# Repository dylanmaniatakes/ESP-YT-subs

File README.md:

# ESP YouTube Subscriber Counter

A compact, Wi-Fi-connected YouTube subscriber counter for a Seeed Studio **XIAO ESP32-C6** and a 480×320 SPI display with an ILI9488-compatible controller and XPT2046/ADS7846-compatible touch controller.

The device shows the public subscriber count, total views, public video count, connection status, and an Eastern-time clock. It stores Wi-Fi and YouTube API credentials only in the ESP32's internal preferences; no credentials are committed to this repository.

## What you need

- Seeed Studio XIAO ESP32-C6
- 480×320 SPI display with an ILI9488-compatible controller and XPT2046/ADS7846-compatible touch controller
- USB-C **data** cable — not a charge-only cable
- Jumper wires or the optional KiCad carrier board
- 3.3 V logic; do **not** connect a 5 V-only display directly

The display wiring is documented in [`hardware/xiao_c6_tinylcd_bottom_wiring.svg`](hardware/xiao_c6_tinylcd_bottom_wiring.svg).

## Choose how to install the firmware

There are three ways to put the firmware on the XIAO:

1. **Use the hosted web flasher** — easiest; no command line.
2. **Use the local web flasher** — useful offline or for testing.
3. **Build and upload with Arduino** — useful if you want to modify the firmware.

### Option 1: Hosted web flasher (recommended)

This is the easiest path if you only want to use the project. You do not need Arduino, a terminal, or a custom build.

Web Serial is the browser feature that lets a web page ask permission to use the XIAO’s USB serial connection. Chrome, Brave, and Edge support it.

Open this page on the computer connected to the XIAO:

[Open the ESP-YT web flasher](https://dylanmaniatakes.github.io/ESP-YT-subs/web/)

Then:

1. Connect the XIAO to the computer with a USB-C data cable.
2. Click **Start flashing**.
3. When the browser asks for a serial port, select the XIAO.
4. Wait for the progress bar to reach 100%.
5. Unplug and reconnect the XIAO.

A few things are normal:

- The browser may list other serial devices, including Bluetooth devices. Choose only the XIAO.
- If the XIAO does not appear, hold its **BOOT** button while plugging it in, then click **Try again**.
- The flasher checks the bundled firmware’s SHA-256 checksum and refuses to flash a non-ESP32-C6 chip.

Because the hosted page is served over HTTPS, the browser can open the normal Web Serial device chooser.

### Option 2: Local web flasher

Use this if you want an offline copy or do not want to use the hosted page.

1. Start a small local web server from the repository root:

   ```sh
   python3 -m http.server 8000
   ```

2. Open:

   <http://127.0.0.1:8000/web/>

3. Click **Start flashing** and choose the XIAO in the browser prompt.
4. Wait for the progress bar to finish, then unplug and reconnect the device.

Do **not** open `web/index.html` directly from Finder or VS Code. Web Serial needs the `http://127.0.0.1` origin, so the device chooser will not appear from a `file://` page.

### Option 3: Build and upload with Arduino

Use this if you want to change the firmware.

1. Install [Arduino IDE 2](https://www.arduino.cc/en/software) or [Arduino CLI](https://arduino.github.io/arduino-cli/).
2. Install the **esp32** board package.
3. Select the **XIAO_ESP32C6** board.
4. Use the bundled Adafruit GFX and Adafruit BusIO libraries in [`libraries/`](libraries/), or install those two libraries through the Arduino Library Manager.

#### Arduino IDE

1. Open `firmware/esp_yt_subscriber_counter/esp_yt_subscriber_counter.ino`.
2. Select **XIAO_ESP32C6**.
3. Click **Verify**, then **Upload**.

#### Arduino CLI

```sh
arduino-cli compile \
  --fqbn esp32:esp32:XIAO_ESP32C6:PartitionScheme=huge_app \
  --libraries libraries \
  --output-dir build/esp_yt_subscriber_counter \
  firmware/esp_yt_subscriber_counter

arduino-cli upload \
  --port /dev/YOUR_SERIAL_PORT \
  --fqbn esp32:esp32:XIAO_ESP32C6:PartitionScheme=huge_app \
  --input-dir build/esp_yt_subscriber_counter
```

Replace `/dev/YOUR_SERIAL_PORT` with your actual serial port.

## First-run setup

The firmware does not contain your Wi-Fi password, YouTube handle, or API key.

1. Power the counter.
2. Join the `ESP-YT-Setup` Wi-Fi hotspot.
3. Enter the hotspot password: `setup-subs`.
4. Open `http://192.168.4.1/`.
5. Select your Wi-Fi network, enter its password, enter your YouTube channel handle, and paste your YouTube Data API v3 key.
6. Save.

The counter reboots, joins your network, and starts showing your public channel statistics.

To reset the saved setup later, hold the XIAO’s **BOOT** button while powering it on. The device will clear its saved settings and return to the setup hotspot.

## Features

- Public YouTube channel statistics using YouTube Data API v3
- Captive Wi-Fi setup portal on first boot
- Automatic retry after network, DNS, time, or API failures
- Single tap to switch between the subscriber dashboard and clock
- Double tap to rotate the display 180°
- BOOT-button reset for saved settings
- Optional KiCad carrier board for a cleaner build

## API key notes

Create a YouTube Data API v3 key from [Google Cloud Console](https://console.cloud.google.com/), and restrict it to YouTube Data API v3.

Do not put the API key in the source code. The device asks for it during first-run setup and stores it locally.

## Optional KiCad carrier board

The editable KiCad project is in [`hardware/tinylcd_xiao_ups_carrier_r2/`](hardware/tinylcd_xiao_ups_carrier_r2/README.md).

- KiCad schematic ERC and PCB DRC pass with no reported errors.
- The routed PCB and manufacturing files are included.
- **This board has not been fully fabricated or bench-tested yet.** Treat it as an unverified design until you have built and tested your own copy.
- If you use the 18650 backup-power circuit, follow the safety procedure in the hardware README.

## Repository layout

```text
firmware/esp_yt_subscriber_counter/  Counter firmware
firmware/xiao_c6_ili9488_test/       Display diagnostic firmware
hardware/                            Wiring diagram and KiCad carrier project
releases/                           Prebuilt merged firmware for the web flasher
web/                                Local Web Serial flasher
libraries/                           Bundled Adafruit graphics libraries
```

## License

Project code and hardware files are released under the [MIT License](LICENSE). Bundled third-party libraries retain their own licenses in their respective folders.

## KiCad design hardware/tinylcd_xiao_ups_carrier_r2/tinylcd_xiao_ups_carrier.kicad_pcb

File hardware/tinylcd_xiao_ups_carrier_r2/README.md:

# TinyLCD + XIAO ESP32-C6 18650 UPS carrier R2

This is the corrected 100 x 60 mm, two-layer R2 carrier for the subscriber counter. It holds the XIAO ESP32-C6 in removable 2.54 mm sockets, presents the TinyLCD P9 wiring on one straight 1x11 male header, and adds protected single-cell 18650 charging and automatic backup power.

R2 corrects the R1 right-side XIAO socket ordering. With the XIAO component side up and USB-C toward the board's `USB-C` marking, J2 is `VBUS, GND, 3V3, D10, D9, D8, D7` from top to bottom.

The PCB silkscreen includes a neutral project mark. This branding is independent of the firmware's configurable YouTube channel handle.

The backside silkscreen labels every XIAO socket position. J1 is marked `D0` through `D6`; J2 is marked `5V`, `GND`, `3V3`, `D10`, `D9`, `D8`, and `D7`, starting at the USB-C end.

The P9 display header is labeled the same way on the backside, with `3V3`, `RS`, `MOSI`, `CS`, `SCLK`, `RST`, `BL`, `GND`, `T_IRQ`, `T_CS`, and `T_DOUT` printed beside their corresponding pins.

## Status

- KiCad 10 schematic ERC: **0 errors, 0 warnings**
- KiCad 10 PCB DRC: **0 violations, 0 unconnected pads**
- Fully routed two-layer PCB and filled ground planes
- Gerber/drill order ZIP, JLCPCB BOM, and JLCPCB component placement file generated
- Existing display-to-XIAO signal mapping comes from the physically working subscriber counter
- The display plug is assumed to be the photographed 1x11 **2.54 mm Dupont-style** female connector. Check its pitch with a ruler or calipers before ordering; the photos cannot prove the mechanical pitch to manufacturing tolerance.
- **R2 has passed local CAD checks but has not yet been fabricated or electrically bench-tested. Inspect the fabrication preview before ordering.**

## Files

- `tinylcd_xiao_ups_carrier.kicad_pro` — open this project in KiCad
- `tinylcd_xiao_ups_carrier.kicad_sch` — editable schematic
- `tinylcd_xiao_ups_carrier.kicad_pcb` — routed PCB
- `renders/tinylcd_xiao_ups_carrier_schematic.pdf` — printable schematic
- `drc_report.txt` and `erc_report.txt` — final KiCad check reports
- `manufacturing/tinylcd_xiao_ups_carrier_r2_gerbers.zip` — upload this for bare boards
- `manufacturing/jlcpcb_bom.csv` — top-side SMT assembly BOM
- `manufacturing/jlcpcb_cpl.csv` — top-side SMT placement file
- `manufacturing/manual_parts.csv` — parts to solder after JLCPCB assembly
- `manufacturing/single_board_hand_assembly_bom.csv` — one-board shopping BOM with current supplier links
- `manufacturing/lcsc_upload_bom_single_board.csv` — LCSC upload BOM using order quantities that meet the listed minimums
- `manufacturing/digikey_upload_bom_single_board.csv` — DigiKey upload BOM for the exact battery holder
- `SINGLE_BOARD_SHOPPING_LIST.md` — human-readable sourcing and hand-assembly guide

## TinyLCD connector

`J3` is a straight 1x11, 2.54 mm male header. The board silkscreen marks **P9 PIN 1**. Pin 1 is the end nearest the XIAO/USB-C label.

| P9 pin | TinyLCD label | Carrier destination | Default |
|---:|---|---|---|
| 1 | 3V3 | XIAO 3V3 | Connected |
| 2 | RS | XIAO D0 / GPIO0 | Connected |
| 3 | MOSI | XIAO D10 / GPIO18 | Connected |
| 4 | CS | XIAO D9 / GPIO20 | Connected |
| 5 | SCLK | XIAO D8 / GPIO19 | Connected |
| 6 | RST | XIAO D3 / GPIO21 | Connected |
| 7 | BL | SJ1 to 3V3 | Open |
| 8 | GND | GND | Connected |
| 9 | T_IRQ | SJ2 to XIAO D1 | Open |
| 10 | T_CS | SJ3 to XIAO D2 | Open |
| 11 | T_DOUT | SJ4 to XIAO D4 | Open |

Leave `SJ1` open. For touch operation, close `SJ2`, `SJ3`, and `SJ4`, or use temporary jumpers for the equivalent connections: `T_IRQ` to XIAO D1, `T_CS` to D2, and `T_DOUT` to D4. LCD MOSI/D10 and SCLK/D8 are shared with the touch controller.

## Power design

The XIAO USB-C connector remains the normal input. Its 5V rail powers the XIAO/display and a TP4056 single-cell charger. With USB absent, the protected cell feeds the XIAO 5V input through a P-channel load switch and SS34 Schottky diode. When USB returns, its higher voltage automatically takes over without back-feeding the cell.

- TP4056 charge current: approximately 400 mA (`R1 = 3.0k`)
- Charge temperature sensing: 10k B3950 NTC beside the holder
- Cell protection: DW01A + FS8205A (over-charge, over-discharge, and over-current protection)
- Additional input protection: 1.1A resettable fuse and reverse-polarity P-MOSFET
- `S1`: disables battery backup only; USB operation and charging remain available
- `S1` drives `Q3`'s gate, so the display current does not pass through the 300 mA switch contacts
- `D2` red: charging; `D3` green: charge complete

This is seamless backup for short power failures, not a regulated 5V boost supply. On battery, the XIAO 5V pin receives approximately the cell voltage minus the Schottky drop. That follows Seeed's documented external-battery-to-5V-pin diode arrangement, but the finished prototype must still be tested across the full cell discharge range with this particular display.

## JLCPCB order

### Bare boards only

1. Upload `manufacturing/tinylcd_xiao_ups_carrier_r2_gerbers.zip` to JLCPCB.
2. Use: 2 layers, 1.6 mm FR-4, 1 oz copper, green solder mask, and HASL lead-free or ENIG.
3. The detected board size should be 100 x 60 mm. Do not continue if the dimensions or outline differ.

### SMT-assembled boards

1. Start with the same Gerber ZIP and enable top-side PCB assembly.
2. Upload `manufacturing/jlcpcb_bom.csv` and `manufacturing/jlcpcb_cpl.csv`.
   The CPL intentionally uses negative Y coordinates to match KiCad's Gerber
   manufacturing-coordinate convention for this board. Do not convert them to
   positive values before uploading.
3. Confirm every designator maps to the expected LCSC part. Inventory and catalog mappings change, so approve substitutions only after matching value, package, pinout, voltage/current ratings, and polarity.
4. Inspect the graphical placement preview. Pay special attention to `D1`, `D2`, `D3`, `Q1`, `Q2`, `Q3`, `U1`, `U2`, and the switch orientation.
5. `B1`, `J1`, `J2`, and `J3` are intentionally omitted from the SMT BOM; install those manually.

## Hand assembly

1. Do **not** install a cell yet.
2. Solder the two 1x7 female headers into `J1` and `J2`. Use the XIAO with temporary male headers as an alignment jig, but do not heat the XIAO excessively.
3. Solder a straight 1x11 male header into `J3`.
4. Solder the Keystone 1042 holder into `B1`, matching its positive contact to the large board `+` mark.
5. Solder male headers to the XIAO and insert it with USB-C toward the board's `USB-C` marking.
6. Keep `SJ1` open. Initially leave the touch links open for the power test; after the display works, close `SJ2`, `SJ3`, and `SJ4` to enable touch.

## First-power test

Li-ion mistakes can cause fire. Use eye protection, a nonflammable work surface, and a current-limited USB source for the first test. Never use a damaged cell, never short the holder, and never insert an 18650 backwards.

1. With no XIAO, display, USB, or cell connected, check for shorts between `SYS_5V`, `3V3`, `PACK_POS`, and GND.
2. Set `S1` to battery OFF. Connect current-limited USB and confirm about 5V at the XIAO 5V socket and no abnormal heating.
3. Remove USB. Verify the holder polarity with a meter, then insert one reputable 3.6/3.7V 18650 in the marked direction.
4. Reconnect USB. Confirm the red charge LED behavior and monitor `U1`, the cell, and the holder for heat. Stop immediately if anything becomes hot, smells unusual, or draws unexpected current.
5. Install the XIAO only after the rail checks pass. Test the dashboard on USB before attaching the display cable.
6. Attach the ribbon with P9 pin 1 aligned to `J3` pin 1. Confirm 3.3V and GND orientation before power-up.
7. Turn battery backup ON, run from USB, then unplug USB. The counter should remain running. Test again with a partly discharged cell before considering the design validated.

## Regeneration note

`tools/generate_board.py` produces the unrouted placement/netlist board; the committed `.kicad_pcb` also includes the final routed copper. Do not run that script over the finished PCB unless you intend to route it again. `tools/generate_schematic.py` requires the third-party `kicad-sch-api` package.

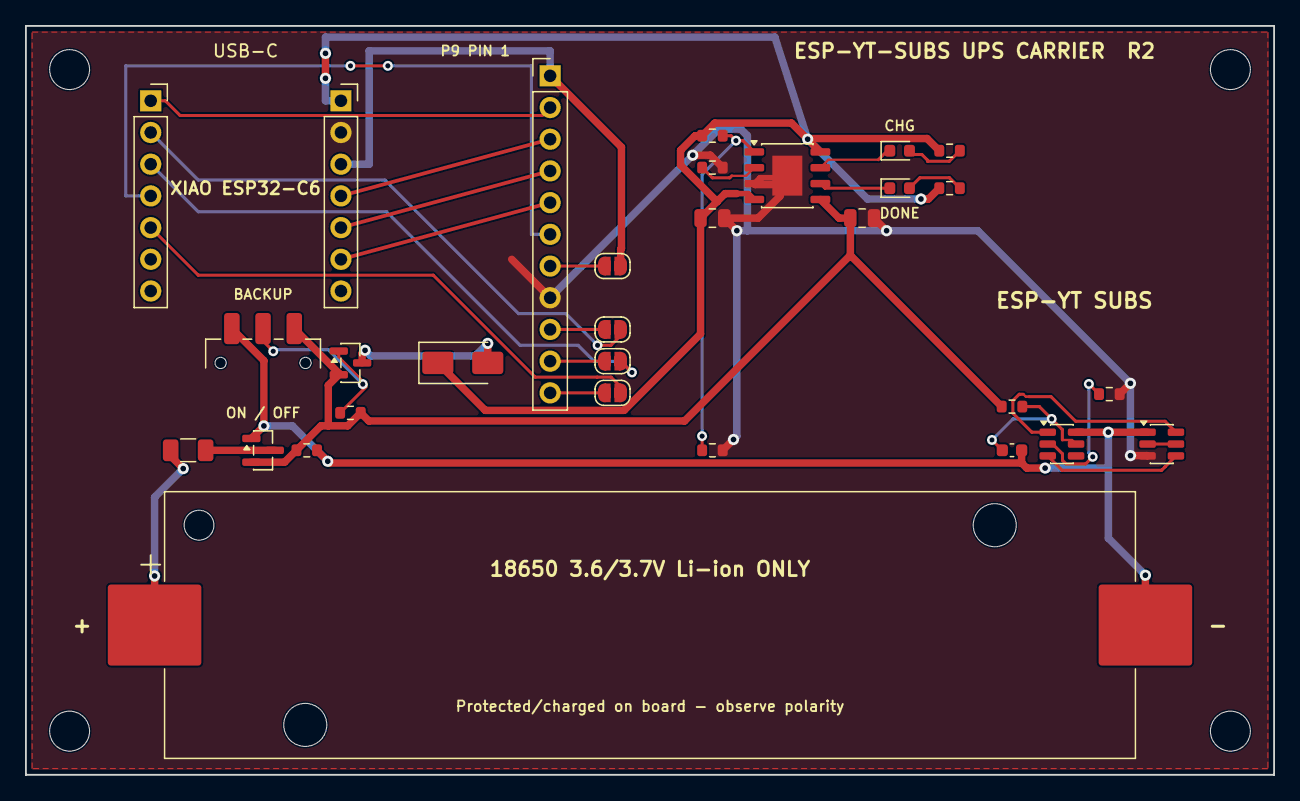
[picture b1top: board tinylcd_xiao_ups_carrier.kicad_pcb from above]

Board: 2 copper layers, 100.0 x 60.0 mm, 34 parts (0 on the bottom side), 32 nets.

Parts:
B1: KEYSTONE_1042_18650; BatteryHolder_Keystone_1042_1x18650
C1, C2: 10uF; C_0805_2012Metric
C3: 100nF; C_0603_1608Metric
D1: SS34; D_SMA
D2: RED_CHARGE; LED_0603_1608Metric
D3: GREEN_DONE; LED_0603_1608Metric
F1: 1.1A_PTC; Fuse_1206_3216Metric
H1, H2, H3, H4: M3; MountingHole_3.2mm_M3
J1: XIAO_LEFT; PinSocket_1x07_P2.54mm_Vertical
J2: XIAO_RIGHT; PinSocket_1x07_P2.54mm_Vertical
J3: TINY_LCD_P9; PinHeader_1x11_P2.54mm_Vertical
Q1, Q3: AO3401A; SOT-23
Q2: FS8205A; SOT-23-6
R1: 3.0k; R_0603_1608Metric
R2: 8.2k; R_0603_1608Metric
R3, R4: 2.2k; R_0603_1608Metric
R5, R8: 1M; R_0603_1608Metric
R6: 100R; R_0603_1608Metric
R7: 1k; R_0603_1608Metric
S1: BATT_ON_OFF; SW_SPDT_CK_JS102011SAQN
SJ1: BL_ENABLE; SolderJumper-2_P1.3mm_Open_RoundedPad1.0x1.5mm
SJ2: TOUCH_IRQ; SolderJumper-2_P1.3mm_Open_RoundedPad1.0x1.5mm
SJ3: TOUCH_CS; SolderJumper-2_P1.3mm_Open_RoundedPad1.0x1.5mm
SJ4: TOUCH_DOUT; SolderJumper-2_P1.3mm_Open_RoundedPad1.0x1.5mm
TH1: NTC_10k_B3950; R_0603_1608Metric
U1: TP4056; HTSOP-8-1EP_3.9x4.9mm_P1.27mm_EP2.4x3.2mm
U2: DW01A; SOT-23-6

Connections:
+3V3: J2.3, J3.1, SJ1.2
BACKUP_GATE: Q3.1, R8.1, S1.2
BATT_SWITCHED: D1.2, Q3.3
CELL_NEG: B1.2, C3.2, Q1.1, Q2.1, R5.2, S1.1, U2.6
CELL_POS: B1.1, F1.1
CELL_POS_FUSED: F1.2, Q1.3
CHRG_LED_A: D2.2, R3.2
CHRG_N: D2.1, U1.7
D0_RS: J1.1, J3.2
D1_TOUCH_IRQ: J1.2, SJ2.2
D2_TOUCH_CS: J1.3, SJ3.2
D3_LCD_RST: J1.4, J3.6
D4_TOUCH_DOUT: J1.5, SJ4.2
D8_SCLK: J2.6, J3.5
D9_LCD_CS: J2.5, J3.4
D10_MOSI: J2.4, J3.3
DONE_LED_A: D3.2, R4.2
DW01_CS: R7.1, U2.2
DW01_OC: Q2.4, U2.3
DW01_OD: Q2.6, U2.1
DW01_VCC: C3.1, R6.2, U2.5
FET_COMMON: Q2.2, Q2.5
GND: C1.2, C2.2, J2.2, J3.8, Q2.3, R1.2, R7.2, TH1.2, U1.3, U1.9
LCD_BL: J3.7, SJ1.1
LCD_T_CS: J3.10, SJ3.1
LCD_T_DOUT: J3.11, SJ4.1
LCD_T_IRQ: J3.9, SJ2.1
PACK_POS: C2.1, Q1.2, Q3.2, R5.1, R6.1, R8.2, S1.3, U1.5
PROG: R1.1, U1.2
STDBY_N: D3.1, U1.6
SYS_5V: C1.1, D1.1, J2.1, R2.1, R3.1, R4.1, U1.4, U1.8
TEMP_SENSE: R2.2, TH1.1, U1.1

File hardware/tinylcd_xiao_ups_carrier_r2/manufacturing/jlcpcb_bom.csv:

Comment,Designator,Footprint,LCSC Part #
10uF 10V X5R,"C1,C2",C_0805_2012Metric,C141033
100nF 50V X7R,C3,C_0603_1608Metric,C14663
SS34,D1,D_SMA,C908680
Red LED,D2,LED_0603_1608Metric,C2286
Green LED,D3,LED_0603_1608Metric,C72043
1.1A resettable fuse,F1,Fuse_1206_3216Metric,C46641027
AO3401A P-channel MOSFET,"Q1,Q3",SOT-23,C700954
FS8205A dual N-channel MOSFET,Q2,SOT-23-6,C2830320
3.0k 1%,R1,R_0603_1608Metric,C2889377
8.2k 0.5%,R2,R_0603_1608Metric,C606177
2.2k 1%,"R3,R4",R_0603_1608Metric,C4190
1M 1%,"R5,R8",R_0603_1608Metric,C22935
100R 1%,R6,R_0603_1608Metric,C22775
1k 1%,R7,R_0603_1608Metric,C21190
JS102011SAQN slide switch,S1,SW_SPDT_CK_JS102011SAQN,C221660
10k B3950 NTC 1%,TH1,R_0603_1608Metric,C49247666
TP4056-42-ESOP8,U1,HTSOP-8-1EP_3.9x4.9mm_P1.27mm_EP2.4x3.2mm,C16581
DW01A,U2,SOT-23-6,C351410
